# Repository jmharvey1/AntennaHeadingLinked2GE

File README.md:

# AntennaHeadingLinked2GE
These are the files used to link a common Antenna Rotor to Google Earth
For an overview of this project, please see YouTube Video found at:
https://youtu.be/OL32_ex3kCU

There is now a second set of files (Arduino sketch, and eagle circuit diagram) that supports
interfacing with an 8 wire CDE HAM III rotator control. 
The Python and Google Earth KLM files are the same for either interface

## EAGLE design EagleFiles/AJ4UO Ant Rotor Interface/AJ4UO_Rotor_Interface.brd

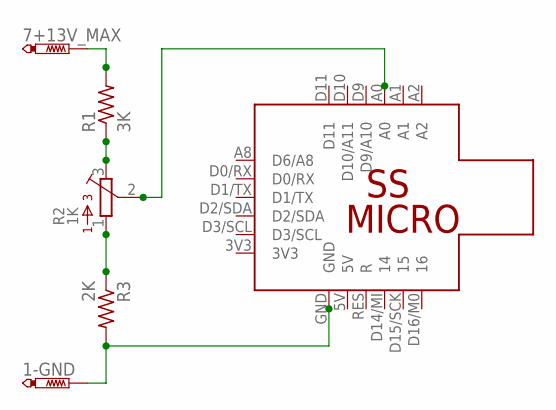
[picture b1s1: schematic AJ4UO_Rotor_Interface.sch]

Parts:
1-GND: 1 - GND; P1-20Y
7+13V_MAX: PTR1PAD1-20Y; P1-20Y
R1: 3K; 0309/10
R2: 1K; 3362P
R3: 2K; 0309/10
U$1: SS_MICRO

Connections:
unnamed: 1-GND.TP, R3.2, U$1.GND
unnamed: R2.1, R3.1
unnamed: R1.1, R2.3
unnamed: 7+13V_MAX.TP, R1.2
unnamed: R2.2, U$1.A0

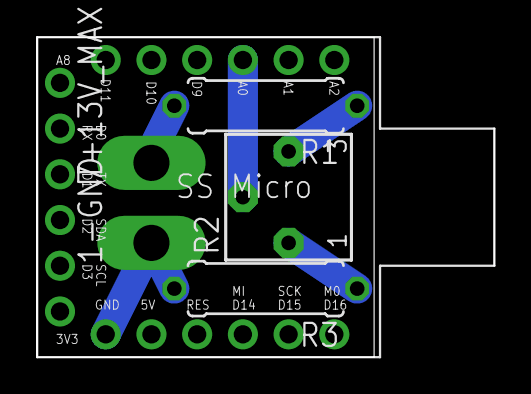
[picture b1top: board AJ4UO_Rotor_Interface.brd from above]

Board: 2 copper layers, 18.7 x 17.8 mm, 6 parts (0 on the bottom side), 5 nets.

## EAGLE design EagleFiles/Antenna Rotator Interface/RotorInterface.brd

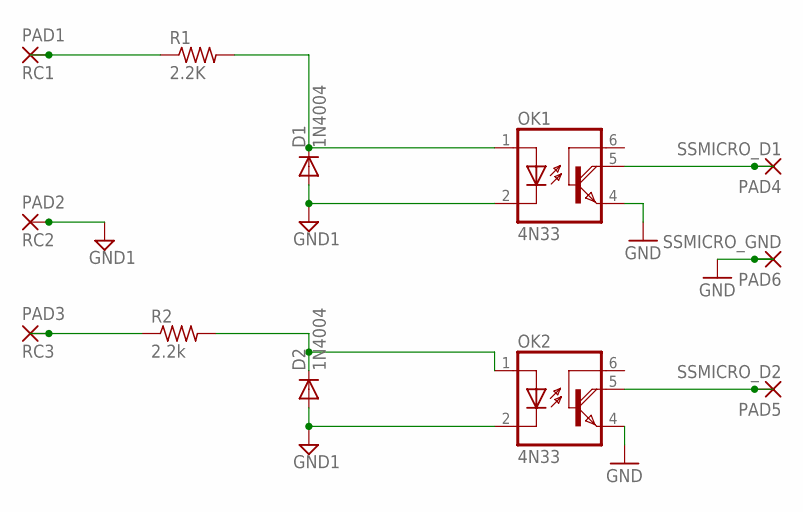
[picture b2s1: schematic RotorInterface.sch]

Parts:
D1, D2: 1N4004; DO41-10
OK1, OK2: 4N33; DIL06
PAD1: RC1; SMD2,54-5,08
PAD2: RC2; SMD2,54-5,08
PAD3: RC3; SMD2,54-5,08
PAD4: SSMICRO_D1; SMD2,54-5,08
PAD5: SSMICRO_D2; SMD2,54-5,08
PAD6: SSMICRO_GND; SMD2,54-5,08
R1: 2.2K; 0309/12
R2: 2.2k; 0309/12

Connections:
GND: OK1.4 (E), OK2.4 (E), PAD6.1
GND1: D1.A, D2.A, OK1.2 (C), OK2.2 (C), PAD2.1
unnamed: PAD3.1, R2.1
unnamed: PAD1.1, R1.1
unnamed: D1.C, OK1.1 (A), R1.2
unnamed: OK1.5 (COL), PAD4.1
unnamed: OK2.5 (COL), PAD5.1
unnamed: D2.C, OK2.1 (A), R2.2

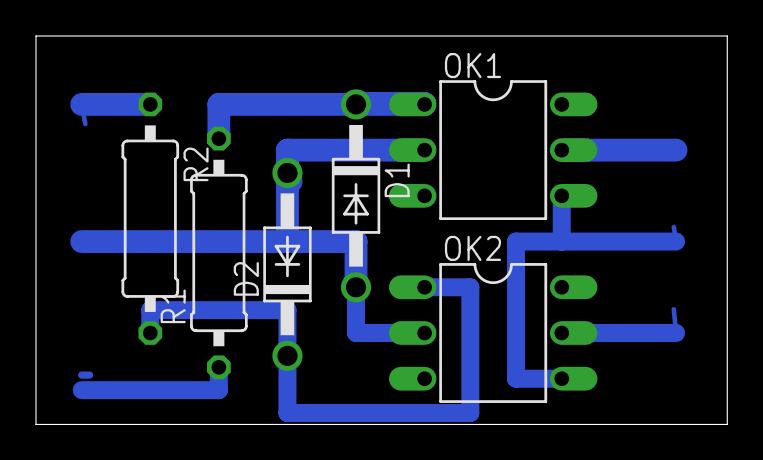
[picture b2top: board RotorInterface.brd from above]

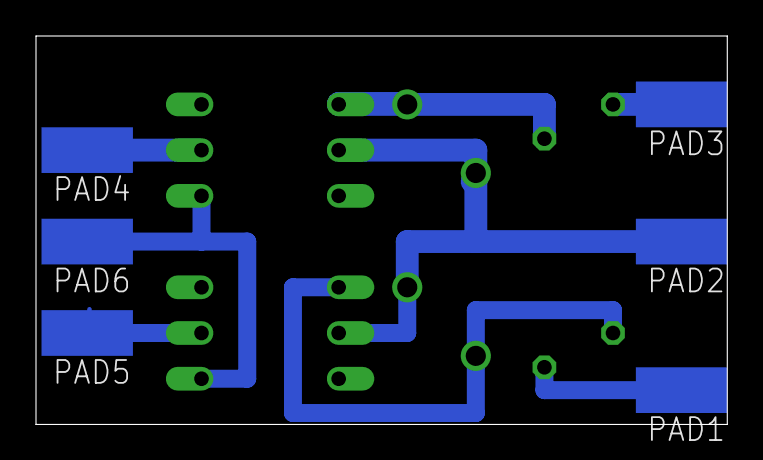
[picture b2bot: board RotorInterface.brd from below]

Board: 2 copper layers, 38.4 x 21.6 mm, 12 parts (6 on the bottom side), 8 nets.

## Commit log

2016-11-18 Initial project files setup
    Install base set of project files
2016-11-18 Updated ReadMe File
    Added YouTUbe Refeerence
2017-02-21 General Instructions to setup local computer to support this Project
    General Instructions to setup local computer to support this Project
2017-02-21 Minor tweaks to general instructions & Python code
2017-02-23 Further revisions to install/setup instructions
    Revised web site references and clarified some instruction steps
2017-02-23 Furhter revisions to the install & setup instructions
    Mainly clarified step 3 and added Google Earth resource prerequesit
2017-02-23 intall & setup revision
2017-02-25 futher refinements to the Install & setuo instructions
    Added better process to link serial library to python
2017-02-25 Further refinements to the install & setup instructions
    added/revised section serial library integration steps
2017-02-27 more tweaks to the install & setup instructions
2017-02-27 Added files to also support interfacing with a CDE HAM III rotator control
2021-07-22 Added .pdf files for original interface board
    Added .pdf files for Eagle interface board (shematic & Layout)
